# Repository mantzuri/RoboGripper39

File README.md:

# RoboGripper39
Team #39 2015 Senior Design project.
This project will contains:

1) 3D design *.cad files of the final design
2) Assamply menual (last pages in the final report)
3) Eagle PCB sketches
4) Arudino code for menual and automatic motion
5) Led controller code
6) LabView GUI controller

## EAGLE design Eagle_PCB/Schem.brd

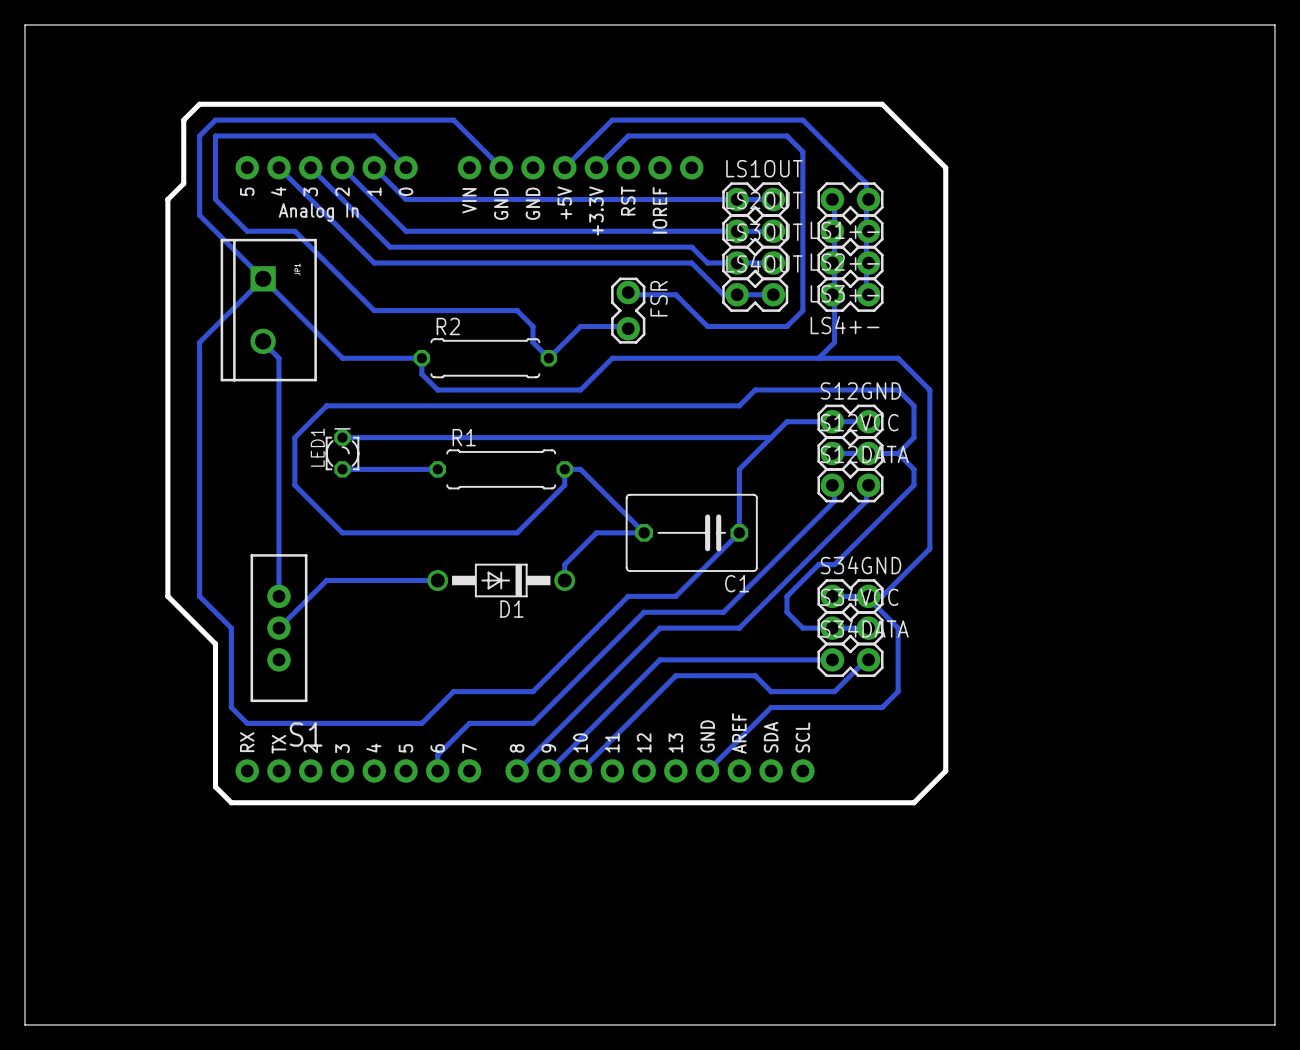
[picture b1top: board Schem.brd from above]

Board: 2 copper layers, 100.0 x 80.0 mm, 23 parts (0 on the bottom side), 5 nets.

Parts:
C1: C075-063X106
D1: 1N4004; DO41-10
FSR: 1X02_LOCK
J1: ARDUINO_R3_SHIELD; UNO_R3_SHIELD
JP1: SCREWTERMINAL-5MM-2
LED1: LED_LD260
LS1+-, LS1OUT, LS2+-, LS2OUT, LS3+-, LS3OUT, LS4+-, LS4OUT: 1X02_LOCK
R1, R2: 0309/10
S1: SWITCH-SPDT
S12DATA, S12GND, S12VCC, S34DATA, S34GND, S34VCC: 1X02_LOCK

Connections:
GND: C1.1, J1.GND@1, J1.GND@2, JP1.1, LED1.K, R2.1
unnamed: C1.2, D1.C, R1.2
unnamed: LED1.A, R1.1
unnamed: D1.A, S1.2
S$3: J1.A0, R2.2

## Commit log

2015-05-03 Create the repo contains the initial codes
2015-05-06 Four servo serial, LabView_GUI files were added
2015-07-13 Create README.md
    Add list of items

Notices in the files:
parts and their libraries:
SparkFun-Connectors: Licensing: Creative Commons ShareAlike 4.0 International - https://creativecommons.org/licenses/by-sa/4.0
